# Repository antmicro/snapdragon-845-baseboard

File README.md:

# Antmicro's open source SA800U (Snapdragon 845) Baseboard

Copyright (c) 2022-2023 [Antmicro](https://www.antmicro.com)

## Overview

This repository contains open hardware design files for an experimental development board for Quectel [SA800-U](https://www.quectel.com/product/sa800u-wf-smart-module) System on Module (SoM) featuring Qualcomm [Snapdragon 845 Mobile Platform](https://www.qualcomm.com/products/application/smartphones/snapdragon-8-series-mobile-platforms/snapdragon-845-mobile-platform).
This development board break-routes the relevant I/O interfaces from the SoM keeping a small mechanical outline. 
The design files were prepared in KiCad.

## Repository structure

The main repository directory contains KiCad PCB project files, a LICENSE and README.
The remaining files are stored in the following directories:

* `lib` - contains the component libraries
* `img` - contains graphics for this README
* `assets` - contains visual assets for showcasing this design on [Open Hardware Portal](https://openhardware.antmicro.com)

## Key Features

* Quectel SA800U with Qualcomm Snapdragon 845
* WiFi and Bluetooth
* Gigabit Ethernet
* Power over Ethernet controller
* HDMI output implemented with on-board DSI-HDMI bridge
* DSI interface exposed on Flexible Flat Cable (FFC) connector
* USB 3.1 (Type-C) connector supporting host/otg mode with optional DisplayPort video output
* USB 3.0 (Type-C) connector working in Downstream Facing (i.e. Host) Mode
* M.2 connector (key M) for optional external storage
* 2x 4-lane MIPI CSI-2 camera interface

The board supports multiple power supply scenarios including:

* Power over Ethernet
* USB-C PD (Power Delivery)
* External PSU or battery

The on-board camera connector is electrically compatible with several video accessories created by Antmicro such as:
 
* [OV9281 Dual Camera Board](https://github.com/antmicro/ov9281-camera-board)
* [SDI-MIPI bridge](https://github.com/antmicro/sdi-mipi-bridge)
* [HDMI-MIPI bridge](https://github.com/antmicro/hdmi-mipi-bridge)

## License

[Apache-2.0](LICENSE)

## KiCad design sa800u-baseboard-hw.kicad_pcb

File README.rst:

=================================
SA800U (Snapdragon 845) Baseboard
=================================

Copyright (c) 2022 `Antmicro <https://www.antmicro.com>`_

.. figure:: img/sa800u-baseboard-vis.png

Overview
--------

This repository contains open hardware design files for an experimental development board for Quectel `SA800-U <https://www.quectel.com/product/sa800u-wf-smart-module>`_ System on Module (SoM) featuring Qualcomm `Snapdragon 845 Mobile Platform <https://www.qualcomm.com/products/application/smartphones/snapdragon-8-series-mobile-platforms/snapdragon-845-mobile-platform>`_.
This development board break-routes the relevant I/O interfaces from the SoM keeping a small mechanical outline. 
The design files were prepared in KiCad.

Repository structure
--------------------
The main repository directory contains KiCad PCB project files, a LICENSE and README.
The remaining files are stored in the following directories:

* ``lib`` - contains the component libraries
* ``img`` - contains graphics for this README

Key Features
------------

* Quectel SA800U with Qualcomm Snapdragon 845
* WiFi and Bluetooth
* Gigabit Ethernet
* Power over Ethernet controller
* HDMI output implemented with on-board DSI-HDMI bridge
* DSI interface exposed on Flexible Flat Cable (FFC) connector
* USB 3.1 (Type-C) connector supporting host/otg mode with optional DisplayPort video output
* USB 3.0 (Type-C) connector working in Downstream Facing (i.e. Host) Mode
* M.2 connector (key M) for optional external storage
* 2x 4-lane MIPI CSI-2 camera interface

The board supports multiple power supply scenarios including:

* Power over Ethernet
* USB-C PD (Power Delivery)
* External PSU or battery

The on-board camera connector is electrically compatible with several video accessories created by Antmicro such as:
 
* `OV9281 Dual Camera Board <https://github.com/antmicro/ov9281-camera-board>`_
* `SDI-MIPI bridge <https://github.com/antmicro/sdi-mipi-bridge>`_
* `HDMI-MIPI bridge <https://github.com/antmicro/hdmi-mipi-bridge>`_

License
=======

`Apache-2.0 <LICENSE>`_

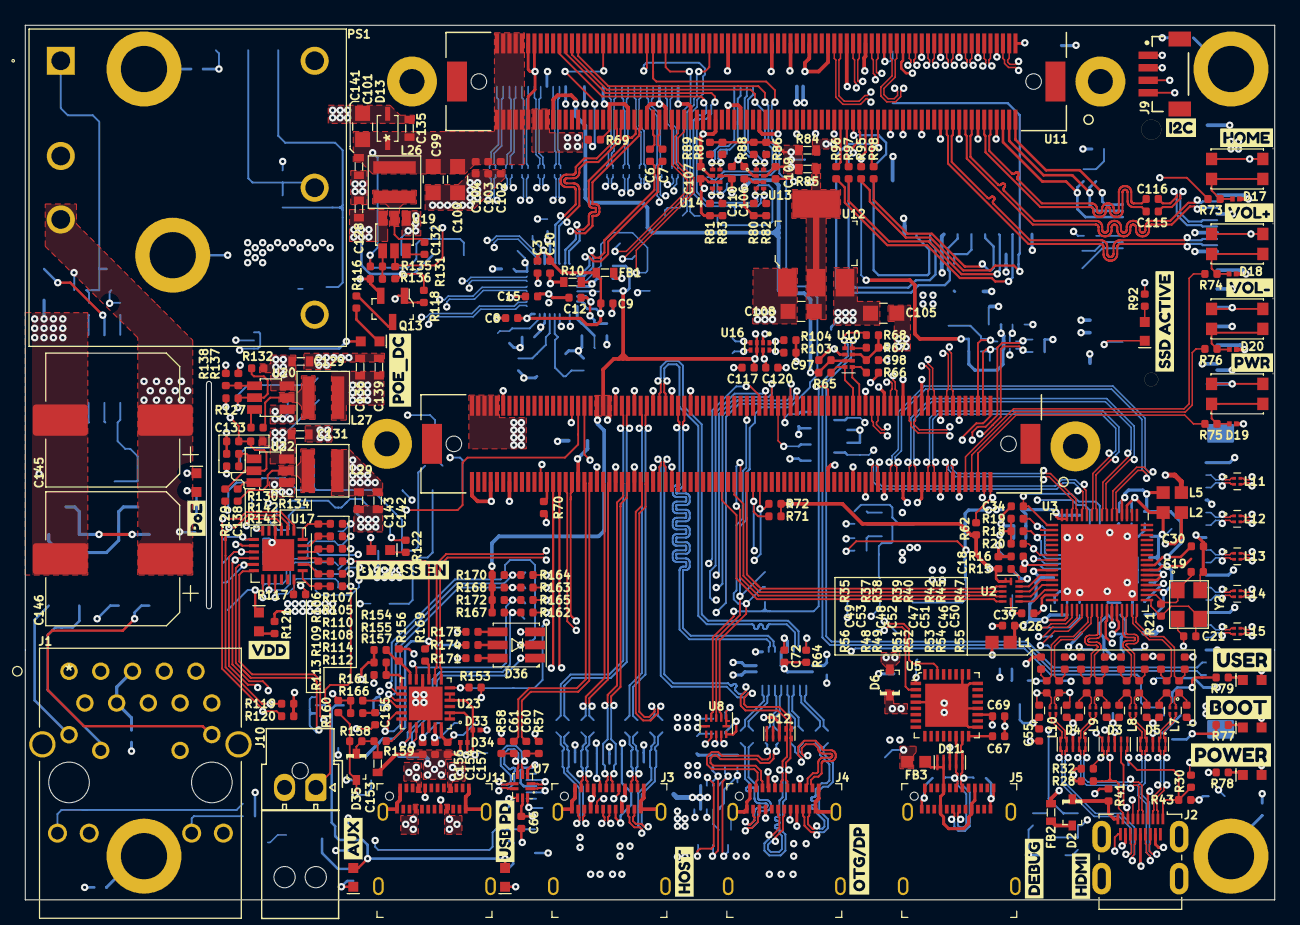
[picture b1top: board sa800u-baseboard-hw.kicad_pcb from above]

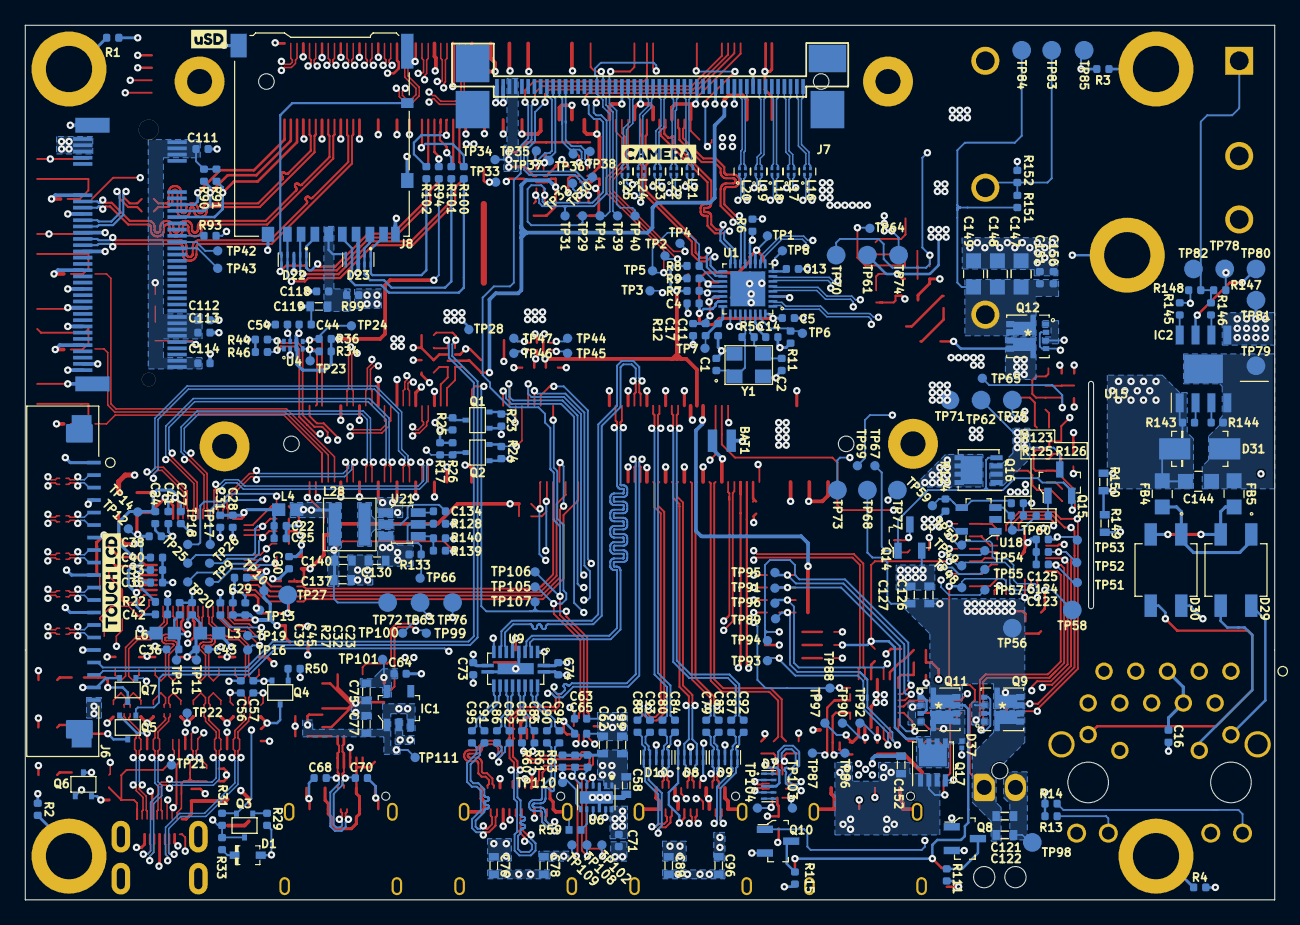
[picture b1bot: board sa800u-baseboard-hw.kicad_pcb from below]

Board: 6 copper layers, 100.0 x 70.0 mm, 603 parts (327 on the bottom side), 418 nets.

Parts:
BAT1: MS621FE-FL11E
C1, C2, C56, C57, C104, C118: C_10p_0402; 0402-cap
C3, C4, C5, C6, C7, C11, C12, C13, C14, C15, C18, C20, C27, C28, C29, C30, C31, C32, C33, C35, C37, C39, C40, C41, C42, C44, C45, C46, C47, C48, C49, C50, C51, C52, C53, C54, C55, C60, C61, C63, C64, C65, C67, C69, C72, C73, C74, C79, C80, C81, C82, C83, C84, C85, C86, C87, C88, C90, C91, C92, C93, C94, C95, C97, C98, C102, C106, C107, C109, C110, C115, C116, C117, C120, C123, C124, C125, C132, C133, C134, C138, C151, C155: C_100n_0402; 0402-cap
C8, C9, C10: C_4u7_0402; 0402-cap
C16: C_10n_0402; 0402-cap
C17, C25, C26, C34, C66, C111, C112, C113, C114, C150, C154, C156, C157: C_1u_0402; 0402-cap
C19, C21: C_15p_0402; 0402-cap
C22, C23, C24, C36, C38, C43, C71: C_10u_0402; 0402-cap
C58, C59, C62, C76, C78, C89, C96: C_47u_0603; 0603-cap
C68, C70: C_47p_0402; 0402-cap
C75, C153: C_1u_0603; 0603-cap
C77, C119: C_2u2_0603; 0603-cap
C99, C100, C101, C147, C148: C_100u_0805; 0805-cap
C103: C_33p_0402; 0402-cap
C105, C108: C_4u7_0805; 0805-cap
C121, C122, C126, C127, C131: C_10u_25V_0603; 0603-cap
C128, C129, C130, C135, C136, C137, C139, C140, C141, C142, C143: C_22u_0603; 0603-cap
C144: C_100n_0805_100V; 0805-cap
C145, C146: C_47u_ELEC_100V; CP_Elec_10x10.5
C149: C_47u_0805; 0805-cap
C152: C_4u7_0603; 0603-cap
D1, D2, D6: 1N4148WS; SOD-323F
D3, D4, D5, D7, D8, D9, D10, D11, D12, D22, D23: PUSB3F96X_PASS; PUSB3F96X
D13: STS321045B502
D14, D15, D16, D21, D24, D25, D26, D27, D28, D32: KP-1608EC; LED_0603
D17, D18, D19, D20: PESD2V5Y1BSFYL; RESC0603X26N
D29, D30: MB10S
D31: SMAJ58A-13-F; DO-214AC
D33, D34, D37: PESD18VF1BSFYL; RESC0603X26N
D35: PMEG6002EJ,115; SOD-323F
D36: ASMB-TTF0-0A20B; PLCC6_3.5x3.7mm
FB1, FB2: BLM18SG121TN1D; 0603-res
FB3: BLM18EG221SN1D; 0603
FB4, FB5: BLM21PG221SN1D; 0805-res
IC1: TPS7A0518PDBVT; SOT-23-5
IC2: TPS2378DDA; SOIC127P600X170-9N
J1: 5-2337992-8
J2: 46756-1001; HDMI_Micro-D_Molex_46765-1x01
J3, J4, J5, J11: 12401598E4_2A; USB-C_Female_12401X
J6: F52R-1A7H1-11020
J7: WE_68715014522
J8: DM3AT-SF-PEJM5; MicroSD_DM3AT-SF-PEJM5
J9: BM04B-SRSS-TB-LF-SN
J10: 1053131202; Molex_Nano-Fit_105313-xx02_1x02_P2.50mm_Horizontal
L1, L2, L3, L4, L5, L6: BRC1608TR35M; INDC1608X100N
L7, L8, L9, L10, L11, L12, L13, L14, L15, L16, L17, L18, L19, L20, L21, L22, L23, L24, L25: NFP0QHB242HS2D; FIL_NFP0QHB242HS2D
L26, L27, L28, L29: XEL4030-222MEC; Coilcraft-XEL4030
M1: SA800U-WF-mechanical_model; SA800U-WF_mechanical_model
M2: M2_2280; m2_2280
PS1: PDQE30-Q48-S5-D; PDQE30-Q48
Q1, Q2, Q3, Q4, Q5, Q6, Q7: BSS138APW; SC70-3
Q8, Q10, Q13, Q14: BSS84; SOT-23-3
Q9, Q11, Q12: Si7223DN; PowerPak-1212
Q15: BSS84PH6327XTSA2; SOT-23-3
Q16, Q17: SQS401EN-T1_BE3; Vishay_PowerPAK_1212-8_Single
R1, R2, R3, R4, R12, R16, R30, R31, R99, R145, R146, R151, R152, R162, R163, R164, R165: R_0R_0402; 0402-res
R5, R21, R118, R119, R120: R_1M0_0402; 0402-res
R6, R8, R17, R29, R41, R50, R77, R78, R79, R90, R91, R93, R111, R115, R116, R121, R122, R127, R128, R130, R131, R132, R133, R134, R138, R139, R142, R153: R_10k_0402; 0402-res
R7, R9, R15, R69, R73, R74, R75, R76, R95, R126, R159: R_1k_0402; 0402-res
R10: R_15k_0603; 0603-res
R11: R_2k49_1%_0402; 0402-res
R13, R14, R158: R_470R_0402; 0402-res
R18, R19, R20, R23, R24, R25, R26, R71, R72, R167, R168, R170, R172: R_4k7_0402; 0402-res
R22: R_7k68_0402; 0402-res
R27, R43, R136, R140: R_20k_0402; 0402-res
R28, R32, R62, R124, R125: R_2k2_0402; 0402-res
R33: R_27k_0402; 0402-res
R34, R36, R44, R46, R65, R66, R67, R68, R80, R81, R82, R83, R86, R87, R88, R89, R103, R104: R_2k_0402; 0402-res
R35, R37, R38, R39, R40, R42, R45, R47: R_50R_0402; 0402-res
R48, R49, R51, R52, R53, R54, R55, R56, R171: R_510R_0402; 0402-res
R57, R58, R60, R61, R63, R94, R147, R148, R154, R155, R156, R157, R160: R_100k_0402; 0402-res
R59: R_100k_0.5%_0402; 0402
R64, R105, R108, R112: R_200k_0402; 0402-res
R70: R_47k_0402; 0402-res
R84, R85: R_0R_0603; 0603-res
R92: R_220R_0402; 0402-res
R96, R97, R98, R100, R101, R102: R_33R_0402; 0402-res
R106, R109, R113: R_39k_0402; 0402-res
R107, R110, R114: R_13k7_0402; 0402-res
R117: R_255k_0402; 0402-res
R123: R_7k5_0402; 0402-res
R129: R_25k5_0402; 0402-res
R135: R_75k_0402; 0402-res
R137: R_31k6_0402; 0402-res
R141: R_52k3_0402; 0402-res
R143: R_24k9_0402; 0402-res
R144: R_63R4_0402; 0402-res
R149: R_20k_0603; 0603-res
R150: R_10k_0603; 0603-res
R161: R_22k_0402; 0402-res
R166: R_100R_0402; 0402-res
R169: R_1k1_0402; 0402-res
R173: R_750R_0402; 0402-res
R174: R_2k7_0402; 0402-res
S1, S2, S3, S4: KMR2; SW_SPST_4.2x2.8
SP1, SP2, SP3, SP4: 9774060151
SP5: 9774040151
TP1, TP2, TP3, TP4, TP5, TP6, TP7, TP8, TP9, TP10, TP11, TP12, TP13, TP14, TP15, TP16, TP17, TP18, TP19, TP20, TP21, TP22, TP23, TP24, TP25, TP26, TP28, TP29, TP30, TP31, TP32, TP33, TP34, TP35, TP36, TP37, TP38, TP39, TP40, TP41, TP42, TP43, TP44, TP45, TP46, TP47, TP48, TP49, TP50, TP51, TP52, TP53, TP54, TP55, TP57, TP59, TP60, TP64, TP65, TP66, TP67, TP69, TP86, TP87, TP88, TP89, TP90, TP91, TP92, TP93, TP94, TP95, TP96, TP97, TP99, TP100, TP101, TP102, TP103, TP104, TP105, TP106, TP107, TP108, TP109, TP110, TP111: TP_SMD_0_75MM; Testpoint_smd_0_75mm
TP27, TP56, TP58, TP61, TP62, TP63, TP68, TP70, TP71, TP72, TP73, TP74, TP75, TP76, TP77, TP78, TP79, TP80, TP81, TP82, TP83, TP84, TP85, TP98: TP; TP-R-1.5
U1: RTL8111H
U2, U8: TXB0104RUT; Texas_R_PUQFN-N12
U3: LT9611
U4, U10, U13, U14, U16: NTS0102GT; PSON50P100X195X50-8N
U5: FT232RQ-REEL; QFN-32-1EP_5x5mm
U6: TPS25820DSST; WSON-12_2x3mm
U7: NX3DV42GU; XQFN10-1.5x1.9mm
U9: CBTL02043ABQ,115; DHVQFN20
U11: SA800U-WF
U12: AP2114H-3_3TRG1; SOT-223
U15: MDT580M01001
U17: LTC4417IUF; LTC4417IUF-TRPBF
U18: LMV431IM5; SOT-23-5
U19, U20, U21, U22: AP62301WU-7; TSOT23-6
U23: STUSB4500QTR; QFN50P400X400X90-25N
Y1: ABM8G-25.000MHZ-18-D2Y-T; KX-7
Y2: ABM8G-24.000MHZ-18-D2Y-T; KX-7
kibuzzard-620E36F2, kibuzzard-620E3512, kibuzzard-620E3570, kibuzzard-620E3688, kibuzzard-620E3711, kibuzzard-620EAFC6, kibuzzard-620EAFCD, kibuzzard-620EAFD5, kibuzzard-620EAFE0, kibuzzard-620EB1D7, kibuzzard-620EB2A6, kibuzzard-620EB07A, kibuzzard-620EB19B, kibuzzard-620EB20E, kibuzzard-620EB24B, kibuzzard-620EB29C, kibuzzard-620EB068, kibuzzard-620EB071, kibuzzard-620EB074, kibuzzard-620EB293, kibuzzard-620EBDB4, kibuzzard-620F4F2B: G***; label

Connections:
1V2_SYS: C137.1, C140.1, L4.1, L5.1, L6.1, L28.2, R139.1, TP72.1
1V2_SYS_EN: R128.1, U11.2_132
1V8_DBG: C64.1, C75.1, IC1.5, TP101.1, U5.1
1V8_SYS: C63.1, U8.1, U8.12
3V3_SYS: C20.1, C54.1, C66.1, C72.1, C73.1, C74.1, C98.1, C111.1, C112.1, C113.1, C114.1, C120.1, C136.1, C139.1, D1.A, FB1.1, J6.20, J9.2, L1.1, L2.1, L3.1, L27.2, R9.1, R15.1, R17.1, R18.1, R19.1, R20.1, R25.1, R26.1, R29.1, R44.2, R46.2, R50.1, R57.2, R67.2, R68.2, R84.2, R90.1, R91.1, R92.1, R93.1, R103.2, R104.2, R137.1, TP71.1, U2.11, U4.7, U7.9, U9.1, U9.6, U9.10, U10.7, U15.2, U15.4, U15.12, U15.14, U15.16, U15.18, U15.70, U15.72, U15.74, U16.7
3V3_SYS_EN: R127.1, U11.2_134
3V8_SYS: C99.1, C100.1, C101.1, C102.1, C103.1, C104.1, C135.1, C141.1, D13.1, L26.2, R135.1, TP70.1, U11.1_159, U11.1_160, U11.1_161, U11.1_162, U11.1_163, U11.1_164, U11.1_165, U11.1_166, U11.1_167, U11.1_168
5V_POE: C147.1, C148.1, C149.1, C150.1, C151.1, PS1.4, Q12.7, Q12.8, R105.1, R151.2, TP50.1, TP84.1, U17.19
5V_SYS: C58.1, C59.1, C62.1, C65.1, C105.1, C130.1, C142.1, C143.1, D6.A, D14.1, D15.1, D16.1, FB2.1, J7.49, J7.50, L29.2, Q16.5, R28.1, R32.1, R60.2, R61.2, R63.2, R133.1, R141.1, R171.2, R173.1, TP28.1, TP63.1, TP73.1, U6.1, U6.2, U8.11, U12.3, U21.3
/Camera Interface/3V3_CAM: C109.1, C110.1, J7.47, J7.48, R84.1, R85.2, R86.2, R87.2, R88.2, R89.2, TP34.1, U13.7, U14.7
/Camera Interface/CCI0_I2C_SCL_3V3: J7.40, R87.1, TP36.1, U14.8
/Camera Interface/CCI0_I2C_SDA_3V3: J7.39, R89.1, TP38.1, U14.1
/Camera Interface/CCI1_I2C_SCL_3V3: J7.42, R86.1, TP35.1, U13.8
/Camera Interface/CCI1_I2C_SDA_3V3: J7.41, R88.1, TP37.1, U13.1
/Camera Interface/CSI0_CLK_FFC_N: J7.28, L25.3
/Camera Interface/CSI0_CLK_FFC_P: J7.29, L25.2
/Camera Interface/CSI0_LN0_FFC_N: J7.25, L24.3
/Camera Interface/CSI0_LN0_FFC_P: J7.26, L24.2
/Camera Interface/CSI0_LN1_FFC_N: J7.23, L23.3
/Camera Interface/CSI0_LN1_FFC_P: J7.24, L23.2
/Camera Interface/CSI0_LN2_FFC_N: J7.21, L22.3
/Camera Interface/CSI0_LN2_FFC_P: J7.22, L22.2
/Camera Interface/CSI0_LN3_FFC_N: J7.19, L21.3
/Camera Interface/CSI0_LN3_FFC_P: J7.20, L21.2
/Camera Interface/CSI1_CLK_FFC_N: J7.10, L20.3
/Camera Interface/CSI1_CLK_FFC_P: J7.11, L20.2
/Camera Interface/CSI1_LN0_FFC_N: J7.7, L19.3
/Camera Interface/CSI1_LN0_FFC_P: J7.8, L19.2
/Camera Interface/CSI1_LN1_FFC_N: J7.5, L18.3
/Camera Interface/CSI1_LN1_FFC_P: J7.6, L18.2
/Camera Interface/CSI1_LN2_FFC_N: J7.3, L17.3
/Camera Interface/CSI1_LN2_FFC_P: J7.4, L17.2
/Camera Interface/CSI1_LN3_FFC_N: J7.1, L16.3
/Camera Interface/CSI1_LN3_FFC_P: J7.2, L16.2
/Ethernet Controller/ETH_1V0: C12.1, C13.1, C14.1, C15.1, C17.1, R12.2, TP8.1, U1.3, U1.8, U1.22, U1.30
/Ethernet Controller/ETH_3V3: C3.1, C4.1, C5.1, C8.1, C9.1, C10.1, FB1.2, R13.2, R14.2, TP1.1, U1.11, U1.23, U1.32
/Ethernet Controller/ETH_ISOLATEB: R9.2, R10.1, TP3.1, U1.20
/Ethernet Controller/ETH_LED0: J1.18, U1.27
/Ethernet Controller/ETH_LED2: J1.16, U1.25
/Ethernet Controller/LAN0_MDI0_N: J1.1, U1.2
/Ethernet Controller/LAN0_MDI0_P: J1.2, U1.1
/Ethernet Controller/LAN0_MDI1_N: J1.3, U1.5
/Ethernet Controller/LAN0_MDI1_P: J1.6, U1.4
/Ethernet Controller/LAN0_MDI2_N: J1.7, U1.7
/Ethernet Controller/LAN0_MDI2_P: J1.8, U1.6
/Ethernet Controller/LAN0_MDI3_N: J1.9, U1.10
/Ethernet Controller/LAN0_MDI3_P: J1.10, U1.9
/Ethernet Controller/PCIE1_RX_C_N: C6.2, U1.18
/Ethernet Controller/PCIE1_RX_C_P: C7.2, U1.17
/Ethernet Controller/REG_1V0: C11.1, R12.1, TP7.1, U1.24
/Ethernet Controller/XTAL1: C1.1, R5.2, U1.28, Y1.1
/Ethernet Controller/XTAL2: C2.1, R5.1, U1.29, Y1.3
/HDMI converter/5V_HDMI: D2.K, J2.19, R41.1
/HDMI converter/5V_HDMI_FB_D: D2.A, FB2.2
/HDMI converter/HDMI_CEC: D3.4, D3.7, J2.15, Q3.3, R31.1, R33.2
/HDMI converter/HDMI_CLK_CONN_N: D4.5, D4.6, J2.14, L10.3
/HDMI converter/HDMI_CLK_CONN_P: D4.4, D4.7, J2.12, L10.2
/HDMI converter/HDMI_CLK_N: C49.1, C57.1, L10.4, R48.1
/HDMI converter/HDMI_CLK_P: C53.1, C56.1, L10.1, R49.1
/HDMI converter/HDMI_DETECT: D3.5, D3.6, J2.1, R30.2, R43.1, TP21.1
/HDMI converter/HDMI_SCL: D3.2, D3.9, J2.17, R28.2, TP16.1, U3.37
/HDMI converter/HDMI_SDA: D3.1, D3.10, J2.18, R32.2, TP19.1, U3.36
/HDMI converter/HDMI_TX0_CONN_N: D4.2, D4.9, J2.11, L9.3
/HDMI converter/HDMI_TX0_CONN_P: D4.1, D4.10, J2.9, L9.2
/HDMI converter/HDMI_TX0_N: C48.1, L9.4, R51.1
/HDMI converter/HDMI_TX0_P: C52.1, L9.1, R52.1
/HDMI converter/HDMI_TX1_CONN_N: D5.5, D5.6, J2.8, L8.3
/HDMI converter/HDMI_TX1_CONN_P: D5.4, D5.7, J2.6, L8.2
/HDMI converter/HDMI_TX1_N: C47.1, L8.4, R53.1
/HDMI converter/HDMI_TX1_P: C51.1, L8.1, R54.1
/HDMI converter/HDMI_TX2_CONN_N: D5.2, D5.9, J2.5, L7.3
/HDMI converter/HDMI_TX2_CONN_P: D5.1, D5.10, J2.3, L7.2
/HDMI converter/HDMI_TX2_N: C46.1, L7.4, R55.1
/HDMI converter/HDMI_TX2_P: C50.1, L7.1, R56.1
/HDMI converter/HDMI_TX_CLK_N: C49.2, R35.2, U3.38
/HDMI converter/HDMI_TX_CLK_P: C53.2, R37.2, U3.39
/HDMI converter/HDMI_TX_D0_N: C48.2, R38.2, U3.40
/HDMI converter/HDMI_TX_D0_P: C52.2, R39.2, U3.41
/HDMI converter/HDMI_TX_D1_N: C47.2, R40.2, U3.45
/HDMI converter/HDMI_TX_D1_P: C51.2, R42.2, U3.46
/HDMI converter/HDMI_TX_D2_N: C46.2, R45.2, U3.47
/HDMI converter/HDMI_TX_D2_P: C50.2, R47.2, U3.48
/HDMI converter/I2C_ADDR: R15.2, R16.1, TP9.1, U3.25
/HDMI converter/LT9611_CEC: Q3.2, R31.2, TP20.1, U3.24
/HDMI converter/LT9611_I2S_D0_SPDIF: U2.7, U3.30
/HDMI converter/LT9611_I2S_MCLK: U2.8, U3.29
/HDMI converter/LT9611_I2S_SCLK: U2.9, U3.28
/HDMI converter/LT9611_I2S_WS: U2.10, U3.27
/HDMI converter/LT9611_INTO_GPIO5: Q1.3, R20.2, R25.2, TP17.1, U3.23
/HDMI converter/LT9611_RST_N: C34.1, Q2.3, R17.2, R26.2, TP18.1, U3.17
/HDMI converter/LT9611_SCL: R19.2, R44.1, TP25.1, U3.18, U4.8
/HDMI converter/LT9611_SDA: R18.2, R46.1, TP26.1, U3.19, U4.1
/HDMI converter/LT9611_VCC12_RX: C24.1, C27.1, C30.1, L5.2, TP14.1, U3.4, U3.56
/HDMI converter/LT9611_VCC12_TX: C36.1, C39.1, L6.2, TP15.1, U3.44
/HDMI converter/LT9611_VCC33_IO: C23.1, C26.1, C29.1, C32.1, L1.2, TP10.1, U3.26, U3.34
/HDMI converter/LT9611_VCC33_RX: C38.1, C40.1, C41.1, C42.1, L2.2, TP12.1, U3.3, U3.51, U3.55
/HDMI converter/LT9611_VCC33_TX: C43.1, C45.1, L3.2, R35.1, R37.1, R38.1, R39.1, R40.1, R42.1, R45.1, R47.1, TP11.1, U3.43
/HDMI converter/LT9611_VDD12: C22.1, C25.1, C28.1, C31.1, C33.1, C35.1, C37.1, L4.2, TP13.1, U3.15, U3.16, U3.31, U3.53, U3.54
/HDMI converter/VCOM: C55.1, Q4.3, R48.2, R49.2, R51.2, R52.2, R53.2, R54.2, R55.2, R56.2, TP22.1, U3.42
/HDMI converter/XTALI: C21.1, R21.2, U3.49, Y2.3
/HDMI converter/XTALO: C19.1, R21.1, U3.50, Y2.1
/LCM/DSI_CLK_L_N: J6.14, L15.1
/LCM/DSI_CLK_L_P: J6.15, L15.4
/LCM/DSI_LN0_L_N: J6.11, L14.1
/LCM/DSI_LN0_L_P: J6.12, L14.4
/LCM/DSI_LN1_L_N: J6.8, L13.1
/LCM/DSI_LN1_L_P: J6.9, L13.4
/LCM/DSI_LN2_L_N: J6.5, L12.1
/LCM/DSI_LN2_L_P: J6.6, L12.4
/LCM/DSI_LN3_L_N: J6.2, L11.1
/LCM/DSI_LN3_L_P: J6.3, L11.4
/LCM/TP_I2C_SCL_3V3: J6.17, R67.1, U10.8
/LCM/TP_I2C_SDA_3V3: J6.18, R68.1, U10.1
/M2/C_PCIE0_TX0_N: C116.1, U15.47
/M2/C_PCIE0_TX0_P: C115.1, U15.49
/Other Interfaces/I2C10_SCL_3V3: J9.4, R103.1, TP46.1, U16.8
/Other Interfaces/I2C10_SDA_3V3: J9.3, R104.1, TP47.1, U16.1
/Other Interfaces/SD_CLK_R: D23.4, D23.7, J8.5, R100.2
/Other Interfaces/SD_CMD_R: D22.1, D22.10, J8.3, R98.2
/Other Interfaces/SD_DATA0_R: D23.2, D23.9, J8.7, R101.2
/Other Interfaces/SD_DATA1_R: D23.1, D23.10, J8.8, R102.2
/Other Interfaces/SD_DATA2_R: D22.4, D22.7, J8.1, R96.2
/Other Interfaces/SD_DATA3_R: D22.2, D22.9, J8.2, R97.2
/Other Interfaces/SD_DET_R: D22.5, D22.6, J8.10, R95.2
/Other Interfaces/SD_VDD_R: C118.1, C119.1, D23.5, D23.6, J8.4, R99.2
/PSU/5V_DC_DC_ENABLE: R129.2, R130.1, R134.2, TP69.1, U22.5
/PSU/AUX_VALID: Q8.1, R120.2, TP57.1, U17.7
/PSU/AUX_VDD: C121.1, C122.1, J10.1, Q9.7, Q9.8, R112.1, TP48.1, U17.21
/PSU/BYPASS_EN: Q14.1, Q15.2, Q16.4, R129.1, TP67.1
/PSU/POE_VALID: Q13.1, R118.2, TP54.1, U17.9
/PSU/USB_PD_VALID: Q10.1, R119.2, TP55.1, U17.8
/PSU/VS1: Q9.1, Q9.3, U17.18
/PSU/VS2: Q11.1, Q11.3, U17.16
/PSU/VS3: Q12.1, Q12.3, U17.14
/PoE/APD: IC2.8, R145.2
/PoE/CDB: IC2.6, R146.1
/PoE/CLS: IC2.3, R144.1
/PoE/DEN: IC2.2, R143.2
/PoE/SMPS_CTRL: PS1.1, R146.2, R147.2, R148.1, TP82.1
/PoE/TRIM: PS1.5, R151.1, R152.1, TP83.1
/PoE/VDD_POE: C144.1, C145.1, C146.1, D31.K, FB4.2, IC2.1, PS1.3, R143.1, R147.1, R149.1, TP78.1
/PoE/VSS_POE: C144.2, D31.A, FB5.2, IC2.4, IC2.9, R144.2, TP79.1
/SoM/BOOT: Q5.1, U11.2_136
/SoM/HOME_KEY_R: D17.1, R73.1, S1.2, S1.4
/SoM/PWR_R: D19.1, R75.1, S3.2, S3.4
/SoM/USER_LED: Q7.1, U11.2_2
/SoM/VOL_DOWN_R: D20.1, R76.1, S4.2, S4.4
/SoM/VOL_UP_R: D18.1, R74.1, S2.2, S2.4
/SoM/VRTC: BAT1.+, U11.2_133
/USB-C Interface /5V0_DBG: C69.1, C77.1, D6.K, FB3.2, IC1.1, IC1.3, TP111.1, U5.19
/USB-C Interface /DBG_USB_D_N: C68.2, D11.1, D11.10, J5.A7, J5.B7, U5.15
/USB-C Interface /DBG_USB_D_P: C70.2, D11.2, D11.9, J5.A6, J5.B6, U5.14
/USB-C Interface /DBG_VBUS: D11.4, D11.5, D11.6, D11.7, FB3.1, J5.A4, J5.A9, J5.B4, J5.B9
/USB-C Interface /USB1C_RX0_C_N: C87.2, D9.2, D9.9, J3.B10
/USB-C Interface /USB1C_RX0_C_P: C92.2, D9.1, D9.10, J3.B11
/USB-C Interface /USB1C_RX1_C_N: C84.1, D10.1, D10.10, J3.A10
/USB-C Interface /USB1C_RX1_C_P: C80.1, D10.2, D10.9, J3.A11
/USB-C Interface /USB1C_TX0_C_N: C79.1, D9.5, D9.6, J3.A3
/USB-C Interface /USB1C_TX0_C_P: C83.1, D9.4, D9.7, J3.A2
/USB-C Interface /USB1C_TX1_C_N: C93.2, D10.4, D10.7, J3.B3
/USB-C Interface /USB1C_TX1_C_P: C88.2, D10.5, D10.6, J3.B2
/USB-C Interface /USB1_SBU_N: D7.4, D7.7, J3.A8, U7.1
/USB-C Interface /USB1_SBU_P: D7.2, D7.9, J3.B8, U7.2
/USB-C Interface /USB2C_RX1_C_N: C90.1, J4.B10
/USB-C Interface /USB2C_RX1_C_P: C94.1, J4.B11
/USB-C Interface /USB2C_RX1_N: C90.2, U9.18
/USB-C Interface /USB2C_RX1_P: C94.2, U9.19
/USB-C Interface /USB2C_RX2_C_N: C86.1, J4.A10
/USB-C Interface /USB2C_RX2_C_P: C82.1, J4.A11
/USB-C Interface /USB2C_RX2_N: C86.2, U9.14
/USB-C Interface /USB2C_RX2_P: C82.2, U9.15
/USB-C Interface /USB2C_TX1_C_N: C81.1, J4.A3
/USB-C Interface /USB2C_TX1_C_P: C85.1, J4.A2
/USB-C Interface /USB2C_TX1_N: C81.2, U9.16
/USB-C Interface /USB2C_TX1_P: C85.2, U9.17
/USB-C Interface /USB2C_TX2_C_N: C95.1, J4.B3
/USB-C Interface /USB2C_TX2_C_P: C91.1, J4.B2
/USB-C Interface /USB2C_TX2_N: C95.2, U9.12
/USB-C Interface /USB2C_TX2_P: C91.2, U9.13
/USB-C Interface /USB2_5V: C71.1, C76.1, C78.1, J4.A4, J4.A9, J4.B4, J4.B9, U6.12
/USB-C Interface /USB2_CC1: J4.A5, U6.9
/USB-C Interface /USB2_CC2: J4.B5, U6.11
/USB-C Interface /USB2_CC_SELECT: R60.1, R64.1, TP110.1, U6.7, U9.9
/USB-C Interface /USB2_EN_5V: TP102.1, U6.4, U8.8
/USB-C Interface /USB2_FAULT_5V: R63.1, TP108.1, U6.5, U8.9
/USB-C Interface /USB2_SINK_5V: R61.1, TP109.1, U6.6, U8.10
/USB-C Interface /USB_SBU_NP_N: C61.2, R58.1, U7.5, U7.7
/USB-C Interface /USB_SBU_NP_P: C60.2, R57.1, U7.4, U7.6
/USB-PD/AB_SIDE: R163.2, R168.1, TP91.1, U23.17
/USB-PD/ALERT: R162.2, R167.1, TP89.1, U23.19
/USB-PD/ATTACH: R165.2, R172.1, TP96.1, U23.11
/USB-PD/GPIO: R164.2, R170.1, TP95.1, U23.15
/USB-PD/PD_CC1: D34.1, J11.A5, TP86.1, U23.1, U23.2
/USB-PD/PD_CC2: D33.1, J11.B5, TP87.1, U23.4, U23.5
/USB-PD/PD_VBUS: C152.1, D35.A, J11.A4, J11.A9, J11.B4, J11.B9, Q17.1, Q17.2, Q17.3, R158.1, R160.1
/USB-PD/STUSB4500_PWR_OK2: D36.1, TP93.1, U23.20
/USB-PD/STUSB4500_PWR_OK3: D36.3, TP94.1, U23.14
/USB-PD/STUSB_VDD: C157.1, TP97.1, U23.24
/USB-PD/VREG_1V2: C156.2, TP92.1, U23.21
/USB-PD/VREG_2V7: C154.1, R154.1, R155.1, TP90.1, U23.23
CAM0_PWDN: J7.32, TP40.1, U11.1_114
CAM0_RST: J7.33, TP39.1, U11.1_100
CAM1_PWDN: J7.34, TP41.1, U11.1_120
CCI0_I2C_SCL: R83.1, TP32.1, U11.1_142, U14.5
CCI0_I2C_SDA: R81.1, TP30.1, U11.1_144, U14.4
CCI1_I2C_SCL: R82.1, TP31.1, U11.1_148, U13.5
CCI1_I2C_SDA: R80.1, TP29.1, U11.1_146, U13.4
CSI0_CLK_N: L25.4, U11.1_30
CSI0_CLK_P: L25.1, U11.1_28
CSI0_LN0_N: L24.4, U11.1_22
CSI0_LN0_P: L24.1, U11.1_24
CSI0_LN1_N: L23.4, U11.1_16
CSI0_LN1_P: L23.1, U11.1_18
CSI0_LN2_N: L22.4, U11.1_10
CSI0_LN2_P: L22.1, U11.1_12
CSI0_LN3_N: L21.4, U11.1_6
CSI0_LN3_P: L21.1, U11.1_4
CSI1_CLK_N: L20.4, U11.1_58
CSI1_CLK_P: L20.1, U11.1_60
CSI1_LN0_N: L19.4, U11.1_52
CSI1_LN0_P: L19.1, U11.1_54
CSI1_LN1_N: L18.4, U11.1_46
CSI1_LN1_P: L18.1, U11.1_48
CSI1_LN2_N: L17.4, U11.1_42
CSI1_LN2_P: L17.1, U11.1_40
CSI1_LN3_N: L16.4, U11.1_34
CSI1_LN3_P: L16.1, U11.1_36
DBG_RXD: TP100.1, U5.30, U11.2_135
DBG_TXD: TP99.1, U5.2, U11.2_137
DSI0_CLK_N: L15.2, U11.2_26
DSI0_CLK_P: L15.3, U11.2_28
DSI0_LN0_N: L14.2, U11.2_38
DSI0_LN0_P: L14.3, U11.2_40
DSI0_LN1_N: L13.2, U11.2_32
DSI0_LN1_P: L13.3, U11.2_34
DSI0_LN2_N: L12.2, U11.2_20
DSI0_LN2_P: L12.3, U11.2_22
DSI0_LN3_N: L11.2, U11.2_14
DSI0_LN3_P: L11.3, U11.2_16
DSI1_CLK_N: U3.9, U11.2_21
DSI1_CLK_P: U3.10, U11.2_19
DSI1_LN0_N: U3.13, U11.2_13
DSI1_LN0_P: U3.14, U11.2_15
DSI1_LN1_N: U3.11, U11.2_37
DSI1_LN1_P: U3.12, U11.2_39
DSI1_LN2_N: U3.7, U11.2_27
DSI1_LN2_P: U3.8, U11.2_25
DSI1_LN3_N: U3.5, U11.2_31
DSI1_LN3_P: U3.6, U11.2_33
EDP_AUX_N: C61.1, U11.2_131
EDP_AUX_P: C60.1, U11.2_129
Earth: C16.2, J1.19, J1.20, R4.1
GND: BAT1.-, C1.2, C2.2, C3.2, C4.2, C5.2, C8.2, C9.2, C10.2, C11.2, C12.2, C13.2, C14.2, C15.2, C17.2, C18.1, C19.2, C20.2, C21.2, C22.2, C23.2, C24.2, C25.2, C26.2, C27.2, C28.2, C29.2, C30.2, C31.2, C32.2, C33.2, C34.2, C35.2, C36.2, C37.2, C38.2, C39.2, C40.2, C41.2, C42.2, C43.2, C44.2, C45.2, C54.2, C55.2, C56.2, C57.2, C58.2, C59.2, C62.2, C63.2, C64.2, C65.2, C66.2, C67.2, C68.1, C69.2, C70.1, C71.2, C72.2, C73.2, C74.2, C75.2, C76.2, C77.2, C78.2, C89.2, C96.2, C97.2, C98.2, C99.2, C100.2, C101.2, C102.2, C103.2, C104.2, C105.2, C106.2, C107.2, C108.2, C109.2, C110.2, C111.2, C112.2, C113.2, C114.2, C117.2, C118.2, C119.2, C120.2, C121.2, C122.2, C123.2, C124.2, C125.2, C126.2, C127.2, C128.2, C129.2, C130.2, C131.2, C135.2, C136.2, C137.2, C139.2, C140.2, C141.2, C142.2, C143.2, C147.2, C148.2, C149.2, C150.2, C151.2, C152.2, C153.2, C154.2, C156.1, C157.2, D3.3, D3.8, D4.3, D4.8, D5.3, D5.8, D7.3, D7.8, D8.3, D8.8, D9.3, D9.8, D10.3, D10.8, D11.3, D11.8, D12.3, D12.8, D13.2, D17.2, D18.2, D19.2, D20.2, D22.3, D22.8, D23.3, D23.8, D27.2, D33.2, D34.2, D36.2, D37.2, IC1.2, J2.4, J2.7, J2.10, J2.13, J2.16, J2.SH, J3.A1, J3.A12, J3.B1, J3.B12, J3.SH, J4.A1, J4.A12, J4.B1, J4.B12, J4.SH, J5.A1, J5.A12, J5.B1, J5.B12, J5.SH, J6.1, J6.4, J6.7, J6.10, J6.13, J6.16, J6.19, J7.9, J7.12, J7.15, J7.18, J7.27, J7.30, J8.6, J8.9, J8.11, J9.1, J10.2, J11.A1, J11.A12, J11.B1, J11.B12, J11.SH, PS1.6, Q4.2, Q5.2, Q6.2, Q7.2, Q8.2, Q10.2, Q13.2, Q14.2, R1.1, R2.1, R3.1, R10.2, R11.2, R16.2, R22.2, R27.2, R41.2, R43.2, R58.2, R59.2, R64.2, R69.2, R70.2, R107.2, R110.2, R114.2, R117.2, R124.2, R130.2, R136.1, R138.2, R140.1, R142.2, R152.2, R153.2, R156.2, R157.2, S1.1, S1.3, S2.1, S2.3, S3.1, S3.3, S4.1, S4.3, SP5.1, TP27.1, TP58.1, TP74.1, TP75.1, TP76.1, TP77.1, TP85.1, TP98.1, U1.33, U2.6, U3.65, U4.2, U5.4, U5.17, U5.20, U5.24, U5.26, U5.33, U6.3, U6.10, U6.13, U7.3, U8.6, U9.2, U9.5, U9.11, U9.20, U9.21, U10.2, U11.1_2, U11.1_7, U11.1_8, U11.1_13, U11.1_14, U11.1_19, U11.1_20, U11.1_25, U11.1_26, U11.1_31, U11.1_32, U11.1_37, U11.1_38, U11.1_41, U11.1_44, U11.1_50, U11.1_56, U11.1_59, U11.1_62, U11.1_65, U11.1_68, U11.1_71, U11.1_74, U11.1_77, U11.1_80, U11.1_83, U11.1_89, U11.1_93, U11.1_94, U11.1_97, U11.1_101, U11.1_105, U11.1_113, U11.1_119, U11.1_125, U11.1_131, U11.1_156, U11.1_157, U11.1_158, U11.2_11, U11.2_12, U11.2_17, U11.2_18, U11.2_23, U11.2_24, U11.2_29, U11.2_30, U11.2_35, U11.2_36, U11.2_41, U11.2_42, U11.2_45, U11.2_53, U11.2_98, U11.2_103, U11.2_104, U11.2_109, U11.2_110, U11.2_115, U11.2_116, U11.2_121, U11.2_122, U11.2_127, U11.2_155, U11.2_158, U11.2_161, U11.2_167, U12.1, U13.2, U14.2, U15.1, U15.3, U15.9, U15.15, U15.21, U15.27, U15.33, U15.39, U15.45, U15.51, U15.57, U15.71, U15.73, U15.75, U15.SH1, U15.SH2, U16.2, U17.10, U17.25, U18.5, U19.1, U20.1, U21.1, U22.1, U23.10, U23.22, U23.25, Y1.2, Y1.4, Y2.2, Y2.4
GNDD: C145.2, C146.2, D32.2, IC2.5, PS1.2, R145.1, R148.2, R150.2, TP81.1
HOME_KEY: R73.2, U11.2_145
I2C4_SCL: R36.1, TP24.1, U4.5, U11.2_6
I2C4_SDA: R34.1, TP23.1, U4.4, U11.2_4
I2C10_SCL: R72.1, TP45.1, U11.2_75, U16.5, U23.7
I2C10_SDA: R71.1, TP44.1, U11.2_77, U16.4, U23.8
I2S1_DATA0: U2.5, U11.2_87
I2S1_MCLK: U2.4, U11.2_81
I2S1_SCK: U2.3, U11.2_83
I2S1_WS: U2.2, U11.2_79
LT9611_GPIO5: Q1.2, R23.2, U11.2_68
LT9611_RST: Q2.2, R24.2, U11.2_70
LVS1A_1V8: C97.1, C106.1, C107.1, R65.2, R66.2, R80.2, R81.2, R82.2, R83.2, U10.3, U10.6, U11.1_149, U13.3, U13.6, U14.3, U14.6
M2_ALERT: R93.2, U15.44
unnamed: C16.1, J1.4, J1.5
unnamed: C67.1, U5.16
unnamed: C108.1, R85.1, TP33.1, U12.2, U12.4
unnamed: C123.1, Q9.2, Q9.4, TP51.1, U17.17
unnamed: C124.1, Q11.2, Q11.4, TP52.1, U17.15
unnamed: C125.1, Q12.2, Q12.4, TP53.1, U17.13
unnamed: C132.1, L26.1, U19.2
unnamed: C132.2, U19.6
unnamed: C133.1, L27.1, U20.2
unnamed: C133.2, U20.6
unnamed: C134.1, L28.1, U21.2
unnamed: C134.2, U21.6
unnamed: C138.1, U22.6
unnamed: C138.2, L29.1, U22.2
unnamed: C153.1, D35.K, R158.2, R159.1
unnamed: C155.2, R166.2
unnamed: D1.K, R33.1
unnamed: D7.1, D7.10
unnamed: D7.5, D7.6
unnamed: D12.4, D12.7
unnamed: D12.5, D12.6
unnamed: D14.2, R77.2
unnamed: D15.2, R78.2
unnamed: D16.2, R79.2
unnamed: D21.1, R92.2
unnamed: D21.2, U15.10
unnamed: D24.2, R111.2
unnamed: D25.2, R115.2
unnamed: D26.2, R116.2
unnamed: D27.1, R121.1
unnamed: D28.2, R122.2
unnamed: D29.1, D30.1, FB4.1
unnamed: D29.2, D30.2, FB5.1
unnamed: D32.1, R149.2, R150.1
unnamed: D36.4, R173.2
unnamed: D36.5, R174.2
unnamed: D36.6, R171.1
unnamed: IC2.7, TP80.1
unnamed: J1.15, R14.1
unnamed: J1.17, R13.1
unnamed: Q3.1, R29.2
unnamed: Q4.1, R50.2
unnamed: Q5.3, R77.1
unnamed: Q6.3, R78.1
unnamed: Q7.3, R79.1
unnamed: Q8.3, R111.1
unnamed: Q10.3, R115.1
unnamed: Q13.3, R116.1
unnamed: Q14.3, R122.1
unnamed: Q15.1, R126.2
unnamed: Q17.4, R160.2, R161.1, R166.1
unnamed: R1.2, SP1.1
unnamed: R2.2, SP2.1
unnamed: R3.2, SP3.1
unnamed: R4.2, SP4.1
unnamed: R11.1, TP6.1, U1.31
unnamed: R22.1, U3.52
unnamed: R27.1, R30.1, U3.35
unnamed: R59.1, U6.8
unnamed: R69.1, U11.1_134
unnamed: R70.1, U11.2_143
unnamed: R105.2, R106.1, U17.5
unnamed: R106.2, R107.1, U17.6
unnamed: R108.2, R109.1, U17.3
unnamed: R109.2, R110.1, U17.4
unnamed: R112.2, R113.1, U17.1
unnamed: R113.2, R114.1, U17.2
unnamed: R117.1, U17.24
unnamed: R123.2, R124.1, TP59.1, U18.4
unnamed: R125.2, R126.1, TP60.1, U18.3
unnamed: R127.2, R132.2, TP65.1, U20.5
unnamed: R128.2, R133.2, TP66.1, U21.5
unnamed: R131.2, TP64.1, U19.5
unnamed: R135.2, R136.2, U19.4
unnamed: R137.2, R138.1, U20.4
unnamed: R139.2, R140.2, U21.4
unnamed: R141.2, R142.1, U22.4
unnamed: R154.2, R156.1, U23.12
unnamed: R155.2, R157.1, U23.13
unnamed: R159.2, U23.18
unnamed: R161.2, U23.16
unnamed: R169.2, U23.9
unnamed: TP42.1, U15.42
unnamed: TP43.1, U15.40
PAIR12: D29.4, J1.11
PAIR36: D29.3, J1.12
PAIR45: D30.4, J1.13
PAIR78: D30.3, J1.14
PCIE0_CLKREQ_N: R91.2, U11.1_5, U15.50
PCIE0_REFCLK_N: U11.1_17, U15.53
PCIE0_REFCLK_P: U11.1_15, U15.55
PCIE0_RST_N: U11.1_1, U15.54
PCIE0_RX_N: U11.1_23, U15.41
PCIE0_RX_P: U11.1_21, U15.43
PCIE0_TX_N: C116.2, U11.1_9
PCIE0_TX_P: C115.2, U11.1_11
PCIE0_WAKE_N: R90.2, U11.1_3, U15.52
PCIE1_CLKREQ_N: R6.2, TP2.1, U1.12, U11.1_109
PCIE1_REFCLK_N: U1.16, U11.1_123
PCIE1_REFCLK_P: U1.15, U11.1_121
PCIE1_RST_N: R8.2, TP5.1, U1.19, U11.1_107
PCIE1_RX_N: C6.1, U11.1_117
PCIE1_RX_P: C7.1, U11.1_115
PCIE1_TX_N: U1.14, U11.1_127
PCIE1_TX_P: U1.13, U11.1_129
PCIE1_WAKE_N: R7.2, TP4.1, U1.21, U11.1_111
PD_VDD: C155.1, D37.1, Q11.7, Q11.8, Q17.5, R108.1, R169.1, R174.1, TP49.1, U17.20
PWRKEY: R75.2, U11.2_5
SBU_SW_OE: R62.1, TP103.1, U7.8, U11.2_1
SBU_SW_SEL: TP104.1, U7.10, U11.2_3
SD_CLK: R100.1, U11.1_45
SD_CMD: R98.1, U11.1_47
SD_DATA0: R101.1, U11.1_51
SD_DATA1: R102.1, U11.1_53
SD_DATA2: R96.1, U11.1_57
SD_DATA3: R97.1, U11.1_55
SD_DET: R94.2, R95.1, U11.1_49
SD_LDO21A: R99.1, U11.1_151, U11.1_153, U11.1_155
STUSB4500_AB_SIDE: R163.1, U11.2_66
STUSB4500_ALERT: R162.1, U11.2_64
STUSB4500_ATTACH: R165.1, U11.2_74
STUSB4500_GPIO: R164.1, U11.2_72
TP_I2C_SCL: R66.1, U10.5, U11.2_44
TP_I2C_SDA: R65.1, U10.4, U11.2_46
USB1_D_N: D8.2, D8.9, J3.A7, J3.B7, U11.2_117
USB1_D_P: D8.4, D8.7, J3.A6, J3.B6, U11.2_119
USB1_SS_RX0_N: C87.1, U11.2_118
USB1_SS_RX0_P: C92.1, U11.2_120
USB1_SS_RX1_N: C84.2, U11.2_114
USB1_SS_RX1_P: C80.2, U11.2_112
USB1_SS_TX0_N: C79.2, U11.2_123
USB1_SS_TX0_P: C83.2, U11.2_125
USB1_SS_TX1_N: C93.1, U11.2_111
USB1_SS_TX1_P: C88.1, U11.2_113
USB2C_HS_D_N: D12.1, D12.10, J4.A7, J4.B7, U11.2_107
USB2C_HS_D_P: D12.2, D12.9, J4.A6, J4.B6, U11.2_105
USB2_EN: TP107.1, U8.4, U11.2_54
USB2_FAULT: TP106.1, U8.3, U11.1_118
USB2_SINK: TP105.1, U8.2, U11.2_80
USB2_SS_RX_N: U9.4, U11.2_100
USB2_SS_RX_P: U9.3, U11.2_102
USB2_SS_TX_N: U9.8, U11.2_108
USB2_SS_TX_P: U9.7, U11.2_106
USB_CC1: D8.5, D8.6, J3.A5, U11.2_141
USB_CC2: D8.1, D8.10, J3.B5, U11.2_139
USB_PD_DISABLE: R153.1, TP88.1, U11.2_76, U23.6
USB_VBUS: C89.1, C96.1, J3.A4, J3.A9, J3.B4, J3.B9, U11.2_160, U11.2_162, U11.2_164, U11.2_166, U11.2_168
VDD: C126.1, C127.1, C128.1, C129.1, C131.1, D24.1, D25.1, D26.1, D28.1, Q9.5, Q9.6, Q11.5, Q11.6, Q12.5, Q12.6, Q15.3, Q16.1, Q16.2, Q16.3, R118.1, R119.1, R120.1, R121.2, R123.1, R125.1, R131.1, R132.1, R134.1, TP56.1, TP61.1, TP62.1, TP68.1, U17.12, U19.3, U20.3, U22.3
VOL_DOWN: R76.2, U11.2_7
VOL_UP: R74.2, U11.2_9
VREG_S4A_1V8: C18.2, C44.1, C117.1, Q1.1, Q2.1, Q6.1, R6.1, R7.1, R8.1, R23.1, R24.1, R34.2, R36.2, R62.2, R71.2, R72.2, R94.1, R167.2, R168.2, R170.2, R172.2, U2.1, U2.12, U4.3, U4.6, U11.2_124, U11.2_126, U11.2_128, U16.3, U16.6

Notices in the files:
parts and their libraries:
Copyright 2021 Accelerated Designs. All rights reserved.
Copyright 2016 Accelerated Designs. All rights reserved.
